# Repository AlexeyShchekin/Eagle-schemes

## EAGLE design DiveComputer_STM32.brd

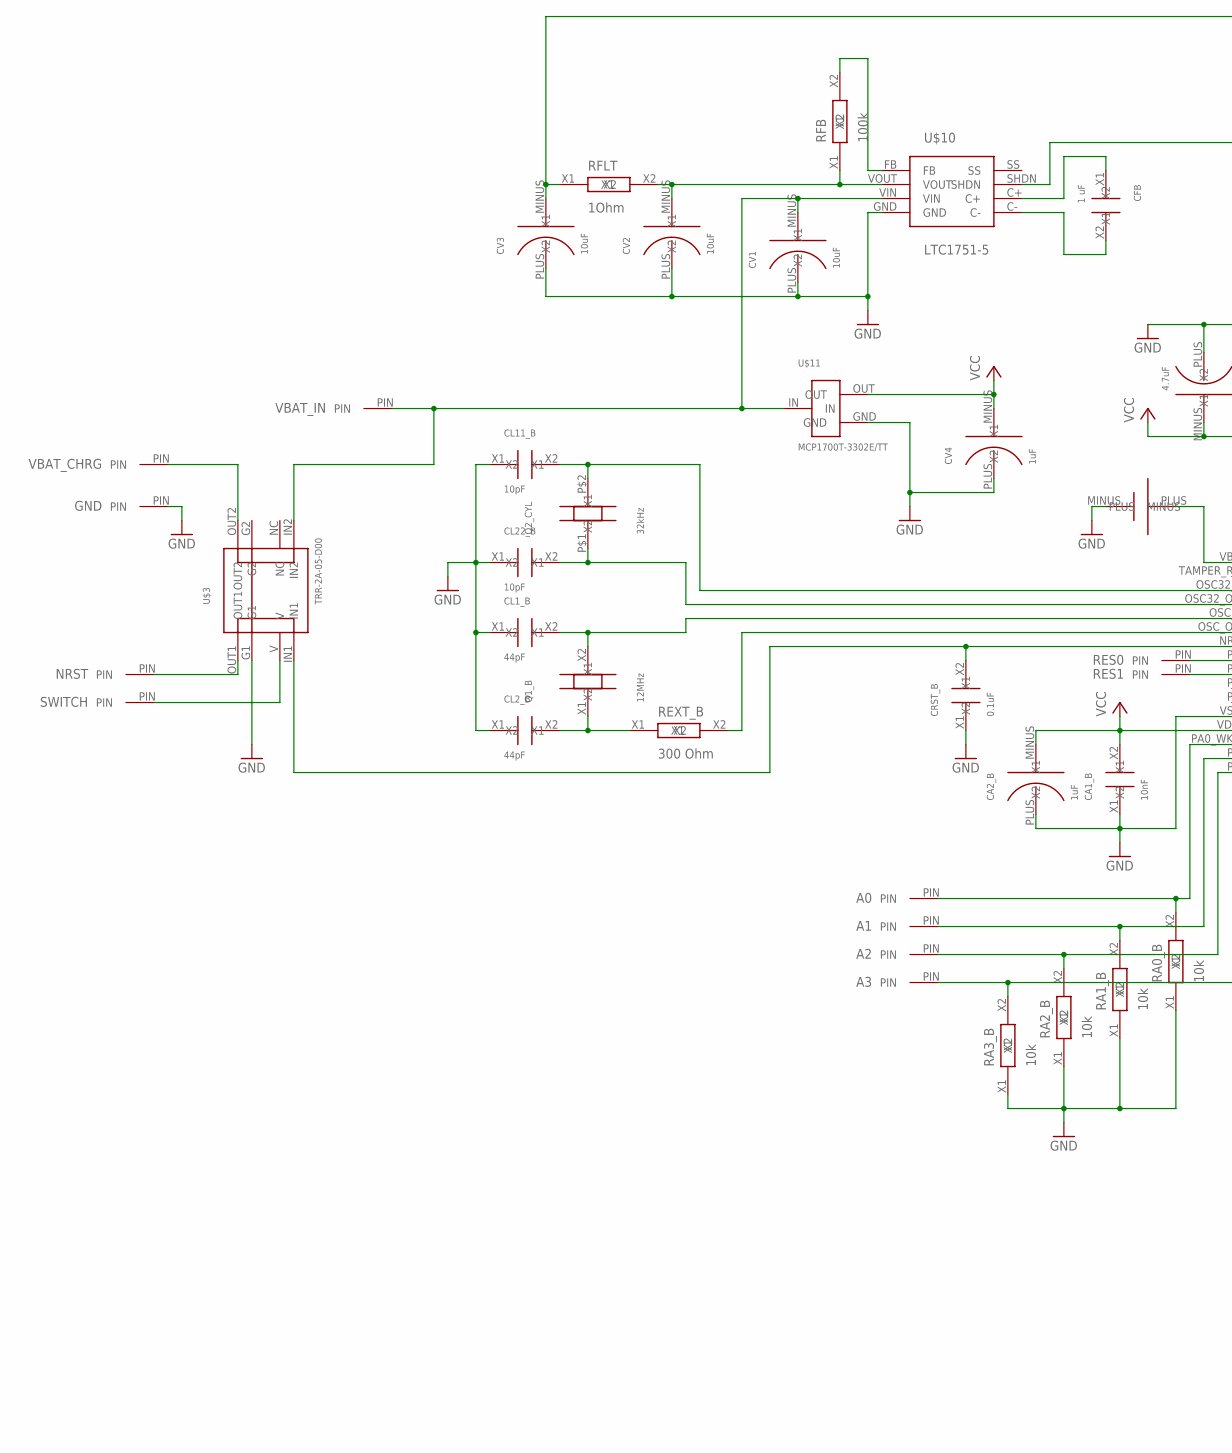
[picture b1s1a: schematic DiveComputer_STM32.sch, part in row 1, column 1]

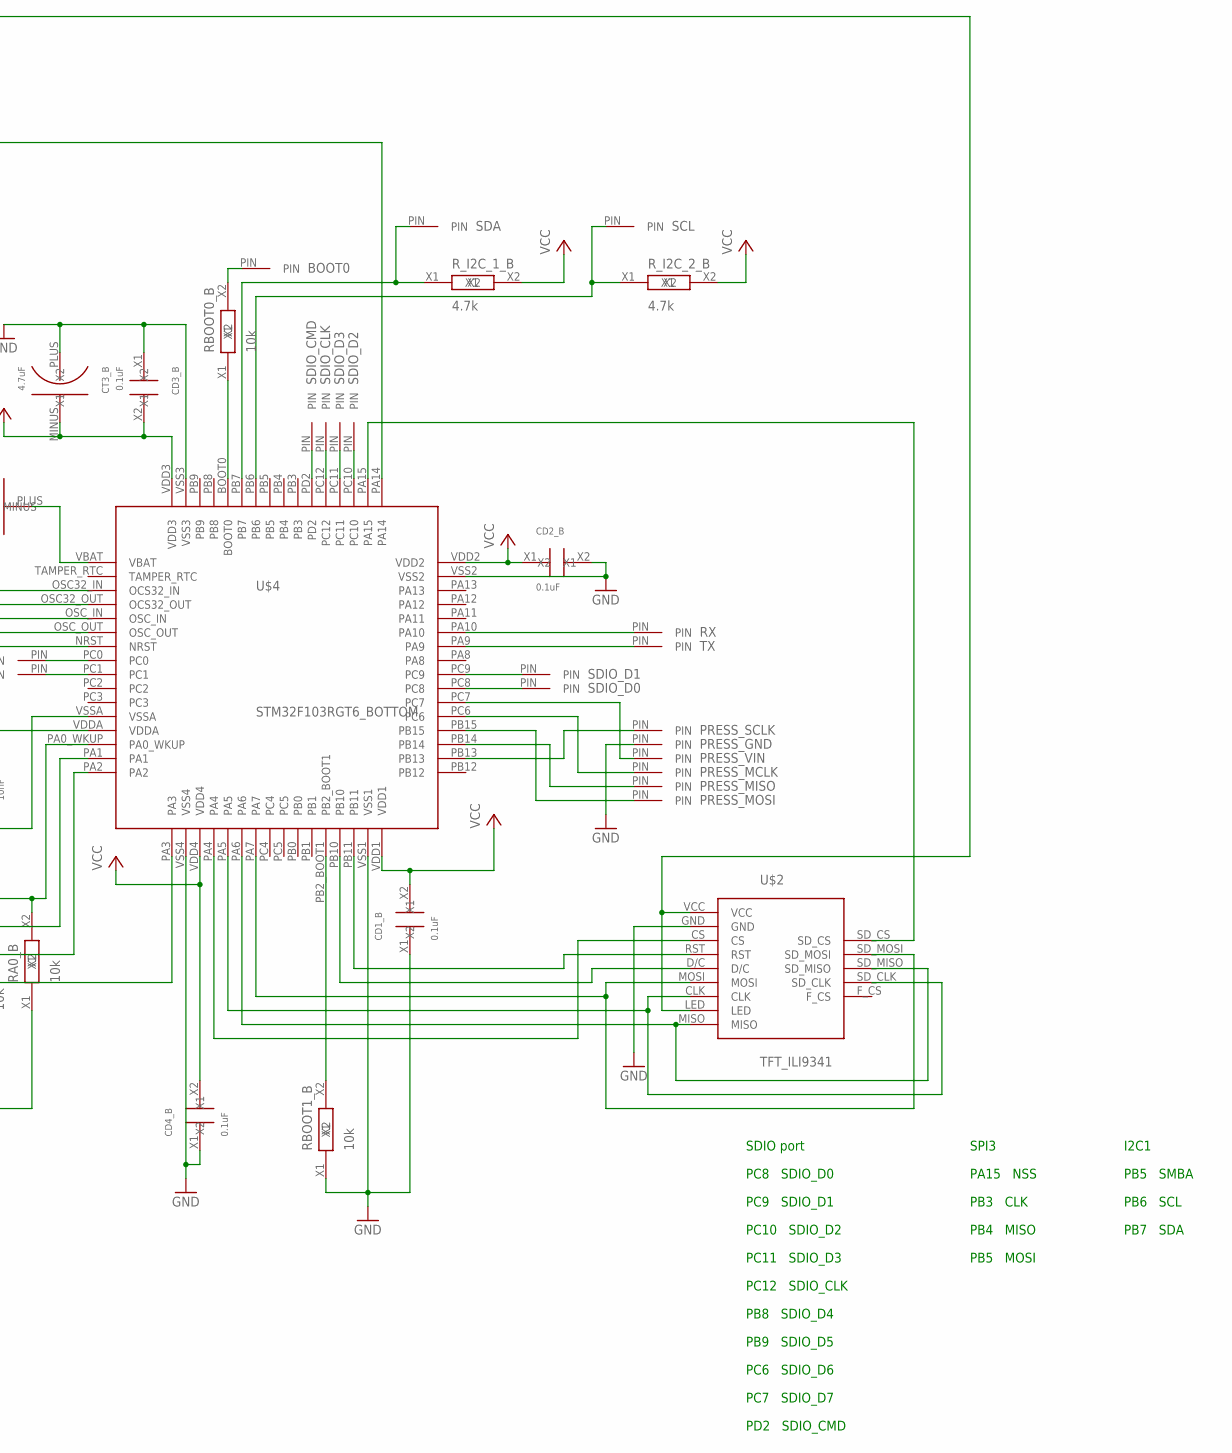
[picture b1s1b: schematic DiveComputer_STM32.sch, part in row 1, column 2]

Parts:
A0, A1, A2, A3: PIN
BOOT0: PIN
CA1_B: 10nF; SMD_2.1X1.25_BOTTOM
CA2_B: 1uF; C_SMD_TA_A_BOTTOM
CD1_B, CD2_B, CD3_B, CD4_B: 0.1uF; SMD_2.1X1.25_BOTTOM
CFB: 1 uF; SMD_2.1X1.25
CL1_B, CL2_B: 44pF; SMD_2.1X1.25_BOTTOM
CL11_B, CL22_B: 10pF; SMD_2.1X1.25_BOTTOM
CRST_B: 0.1uF; SMD_2.1X1.25_BOTTOM
CT3_B: 4.7uF; C_SMD_TA_A_BOTTOM
CV1, CV2, CV3: 10uF; C_SMD_TA_A
CV4: 1uF; C_SMD_TA_A
GND: PIN
NRST: PIN
PRESS_GND: PIN
PRESS_MCLK: PIN
PRESS_MISO: PIN
PRESS_MOSI: PIN
PRESS_SCLK: PIN
PRESS_VIN: PIN
Q1_B: 12MHz; QUARTZ_SMD_BOTTOM
Q2_CYL: 32kHz; QUARTZ_CYL
RA0_B, RA1_B, RA2_B, RA3_B: 10k; SMD_2.1X1.25_BOTTOM
RBOOT0_B, RBOOT1_B: 10k; SMD_2.1X1.25_BOTTOM
RES0, RES1: PIN
REXT_B: 300 Ohm; SMD_2.1X1.25_BOTTOM
RFB: 100k; SMD_2.1X1.25
RFLT: 1Ohm; SMD_2.1X1.25
RX: PIN
R_I2C_1_B, R_I2C_2_B: 4.7k; SMD_2.1X1.25_BOTTOM
SCL: PIN
SDA: PIN
SDIO_CLK: PIN
SDIO_CMD: PIN
SDIO_D0, SDIO_D1, SDIO_D2, SDIO_D3: PIN
SWITCH: PIN
TX: PIN
U$1: VBAT
U$2: TFT_ILI9341
U$3: TRR-2A-05-D00
U$4: STM32F103RGT6_BOTTOM
U$10: LTC1751-5
U$11: MCP1700T-3302E/TT
VBAT_CHRG: PIN
VBAT_IN: PIN

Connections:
GND: CA1_B.X1, CA2_B.PLUS (X1), CD1_B.X1, CD2_B.X2, CD3_B.X1, CD4_B.X1, CL1_B.X1, CL2_B.X1, CL11_B.X1, CL22_B.X1, CRST_B.X1, CT3_B.PLUS (X1), CV1.PLUS (X1), CV2.PLUS (X1), CV3.PLUS (X1), CV4.PLUS (X1), GND.PIN, PRESS_GND.PIN, RA0_B.X1, RA1_B.X1, RA2_B.X1, RA3_B.X1, RBOOT1_B.X1, U$1.MINUS, U$2.GND, U$3.G1, U$4.VSS1, U$4.VSS2, U$4.VSS3, U$4.VSS4, U$4.VSSA, U$10.GND, U$11.GND
unnamed: CL11_B.X2, Q2_CYL.P$2 (X2), U$4.OSC32_IN (OCS32_IN)
unnamed: CL22_B.X2, Q2_CYL.P$1 (X1), U$4.OSC32_OUT (OCS32_OUT)
unnamed: CL2_B.X2, Q1_B.X1, REXT_B.X1
unnamed: CL1_B.X2, Q1_B.X2, U$4.OSC_IN
unnamed: REXT_B.X2, U$4.OSC_OUT
unnamed: CRST_B.X2, U$3.IN1, U$4.NRST
unnamed: U$2.CLK, U$2.SD_CLK, U$4.PA5
unnamed: U$2.MOSI, U$2.SD_MOSI, U$4.PA7
unnamed: U$2.MISO, U$2.SD_MISO, U$4.PA6
unnamed: U$2.CS, U$4.PA4
unnamed: U$2.RST, U$4.PB11
unnamed: U$2.D/C, U$4.PB10
unnamed: A0.PIN, RA0_B.X2, U$4.PA0_WKUP
unnamed: A1.PIN, RA1_B.X2, U$4.PA1
unnamed: A2.PIN, RA2_B.X2, U$4.PA2
unnamed: A3.PIN, RA3_B.X2, U$4.PA3
unnamed: BOOT0.PIN, RBOOT0_B.X2
unnamed: RBOOT1_B.X2, U$4.PB2_BOOT1
unnamed: RBOOT0_B.X1, U$4.BOOT0
unnamed: PRESS_SCLK.PIN, U$4.PB13
unnamed: PRESS_MISO.PIN, U$4.PB14
unnamed: PRESS_MOSI.PIN, U$4.PB15
unnamed: PRESS_MCLK.PIN, U$4.PC6
unnamed: U$2.SD_CS, U$4.PA15
unnamed: U$4.PA14, U$10.SHDN
unnamed: U$3.OUT2, VBAT_CHRG.PIN
unnamed: NRST.PIN, U$3.OUT1
unnamed: CV2.MINUS (X2), RFB.X1, RFLT.X2, U$10.VOUT
unnamed: RFB.X2, U$10.FB
unnamed: CFB.X1, U$10.C+
unnamed: CFB.X2, U$10.C-
unnamed: CV3.MINUS (X2), RFLT.X1, U$2.LED, U$2.VCC
unnamed: CV1.MINUS (X2), U$3.IN2, U$10.VIN, U$11.IN, VBAT_IN.PIN
unnamed: SWITCH.PIN, U$3.V
unnamed: TX.PIN, U$4.PA9
unnamed: RX.PIN, U$4.PA10
unnamed: PRESS_VIN.PIN, U$4.PC7
unnamed: R_I2C_1_B.X1, SDA.PIN, U$4.PB7
unnamed: R_I2C_2_B.X1, SCL.PIN, U$4.PB6
unnamed: U$1.PLUS, U$4.VBAT
unnamed: RES0.PIN, U$4.PC0
unnamed: RES1.PIN, U$4.PC1
unnamed: SDIO_D0.PIN, U$4.PC8
unnamed: SDIO_D1.PIN, U$4.PC9
unnamed: SDIO_CMD.PIN, U$4.PD2
unnamed: SDIO_CLK.PIN, U$4.PC12
unnamed: SDIO_D3.PIN, U$4.PC11
unnamed: SDIO_D2.PIN, U$4.PC10
VCC: CA1_B.X2, CA2_B.MINUS (X2), CD1_B.X2, CD2_B.X1, CD3_B.X2, CD4_B.X2, CT3_B.MINUS (X2), CV4.MINUS (X2), R_I2C_1_B.X2, R_I2C_2_B.X2, U$4.VDD1, U$4.VDD2, U$4.VDD3, U$4.VDD4, U$4.VDDA, U$11.OUT

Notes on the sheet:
SDIO port
PC8 SDIO_D0
PC9 SDIO_D1
PC10 SDIO_D2
PC11 SDIO_D3
PC12 SDIO_CLK
PB8 SDIO_D4
PB9 SDIO_D5
PC6 SDIO_D6
PC7 SDIO_D7
SPI3
PA15 NSS
PB3 CLK
PB4 MISO
PB5 MOSI
I2C1
PB5 SMBA
PB6 SCL
PB7 SDA
PD2 SDIO_CMD

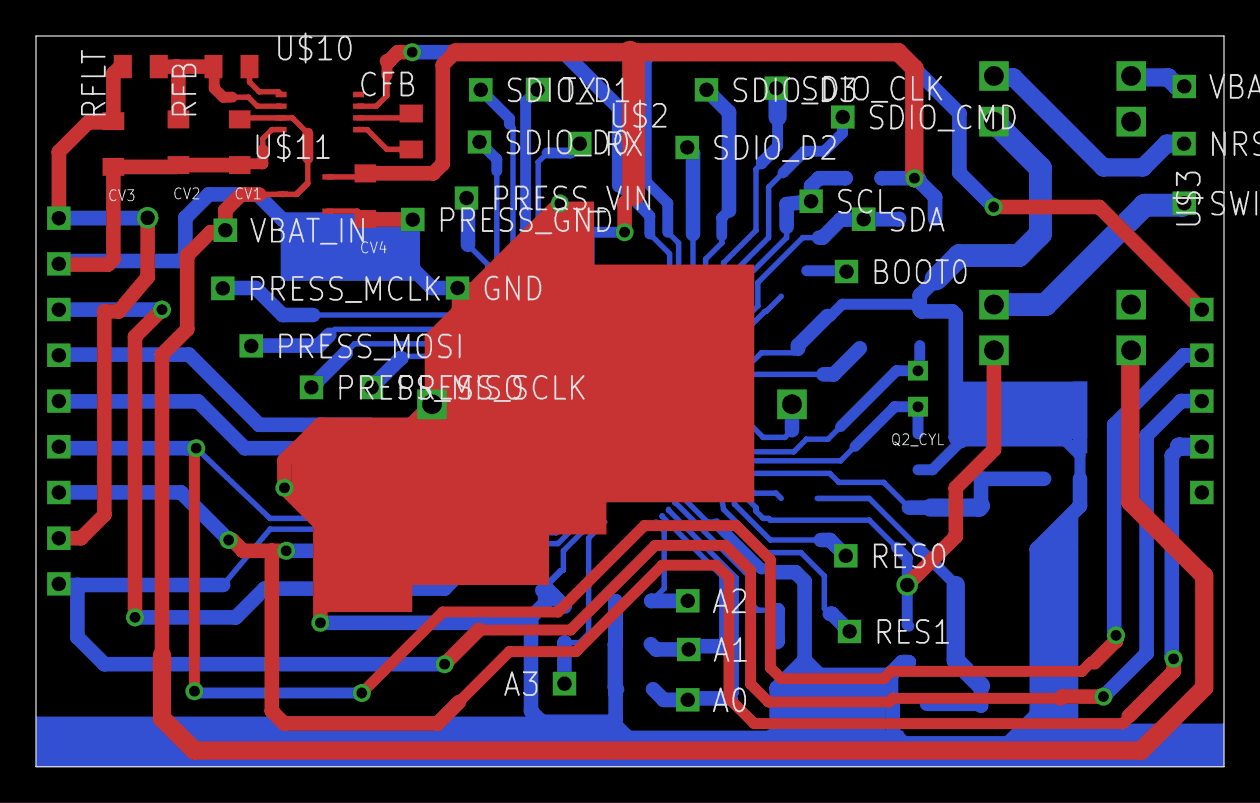
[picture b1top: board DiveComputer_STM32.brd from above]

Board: 2 copper layers, 66.0 x 40.6 mm, 64 parts (0 on the bottom side), 50 nets.

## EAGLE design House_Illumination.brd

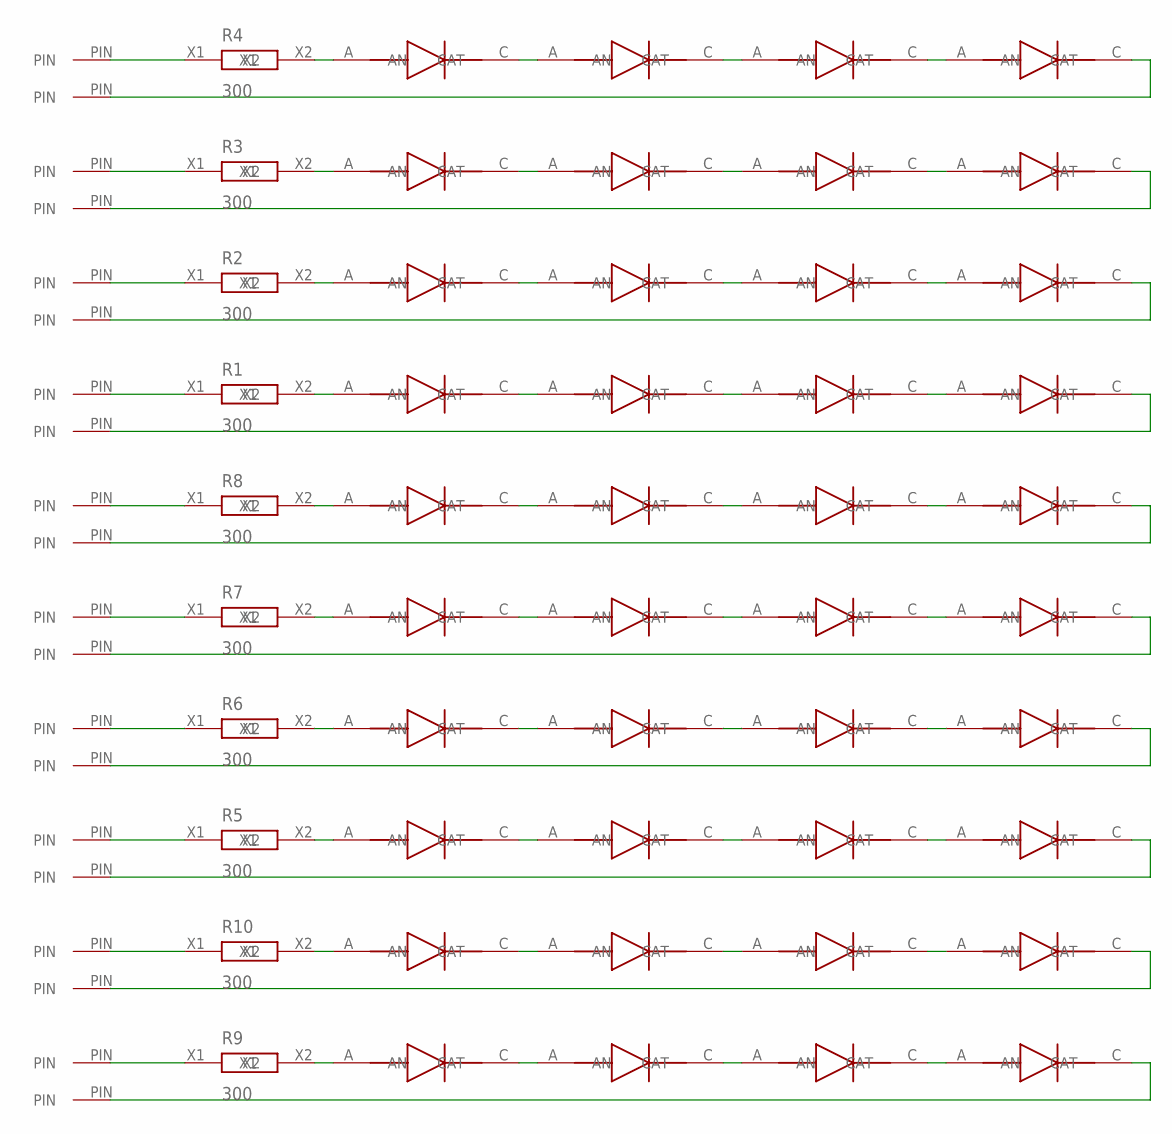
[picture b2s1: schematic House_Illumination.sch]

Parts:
R1, R2, R3, R4, R5, R6, R7, R8, R9, R10: 300; SMD_2.1X1.25
U$1, U$2, U$7, U$8, U$13, U$14, U$19, U$20, U$25, U$26, U$31, U$32, U$37, U$38, U$43, U$44, U$49, U$50, U$55, U$56: PIN_1
U$3, U$4, U$5, U$6, U$9, U$10, U$11, U$12, U$15, U$16, U$17, U$18, U$21, U$22, U$23, U$24, U$27, U$28, U$29, U$30, U$33, U$34, U$35, U$36, U$39, U$40, U$41, U$42, U$45, U$46, U$47, U$48, U$51, U$52, U$53, U$54, U$57, U$58, U$59, U$60: LED0805

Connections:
unnamed: R1.X1, U$1.PIN
unnamed: R1.X2, U$3.A (AN)
unnamed: U$3.C (CAT), U$4.A (AN)
unnamed: U$4.C (CAT), U$5.A (AN)
unnamed: U$5.C (CAT), U$6.A (AN)
unnamed: U$2.PIN, U$6.C (CAT)
unnamed: R2.X1, U$7.PIN
unnamed: R2.X2, U$9.A (AN)
unnamed: U$9.C (CAT), U$10.A (AN)
unnamed: U$10.C (CAT), U$11.A (AN)
unnamed: U$11.C (CAT), U$12.A (AN)
unnamed: U$8.PIN, U$12.C (CAT)
unnamed: R3.X1, U$13.PIN
unnamed: R3.X2, U$15.A (AN)
unnamed: U$15.C (CAT), U$16.A (AN)
unnamed: U$16.C (CAT), U$17.A (AN)
unnamed: U$17.C (CAT), U$18.A (AN)
unnamed: U$14.PIN, U$18.C (CAT)
unnamed: R4.X1, U$19.PIN
unnamed: R4.X2, U$21.A (AN)
unnamed: U$21.C (CAT), U$22.A (AN)
unnamed: U$22.C (CAT), U$23.A (AN)
unnamed: U$23.C (CAT), U$24.A (AN)
unnamed: U$20.PIN, U$24.C (CAT)
unnamed: R5.X1, U$25.PIN
unnamed: R5.X2, U$27.A (AN)
unnamed: U$27.C (CAT), U$28.A (AN)
unnamed: U$28.C (CAT), U$29.A (AN)
unnamed: U$29.C (CAT), U$30.A (AN)
unnamed: U$26.PIN, U$30.C (CAT)
unnamed: R6.X1, U$31.PIN
unnamed: R6.X2, U$33.A (AN)
unnamed: U$33.C (CAT), U$34.A (AN)
unnamed: U$34.C (CAT), U$35.A (AN)
unnamed: U$35.C (CAT), U$36.A (AN)
unnamed: U$32.PIN, U$36.C (CAT)
unnamed: R7.X1, U$37.PIN
unnamed: R7.X2, U$39.A (AN)
unnamed: U$39.C (CAT), U$40.A (AN)
unnamed: U$40.C (CAT), U$41.A (AN)
unnamed: U$41.C (CAT), U$42.A (AN)
unnamed: U$38.PIN, U$42.C (CAT)
unnamed: R8.X1, U$43.PIN
unnamed: R8.X2, U$45.A (AN)
unnamed: U$45.C (CAT), U$46.A (AN)
unnamed: U$46.C (CAT), U$47.A (AN)
unnamed: U$47.C (CAT), U$48.A (AN)
unnamed: U$44.PIN, U$48.C (CAT)
unnamed: R9.X1, U$49.PIN
unnamed: R9.X2, U$51.A (AN)
unnamed: U$51.C (CAT), U$52.A (AN)
unnamed: U$52.C (CAT), U$53.A (AN)
unnamed: U$53.C (CAT), U$54.A (AN)
unnamed: U$50.PIN, U$54.C (CAT)
unnamed: R10.X1, U$55.PIN
unnamed: R10.X2, U$57.A (AN)
unnamed: U$57.C (CAT), U$58.A (AN)
unnamed: U$58.C (CAT), U$59.A (AN)
unnamed: U$59.C (CAT), U$60.A (AN)
unnamed: U$56.PIN, U$60.C (CAT)

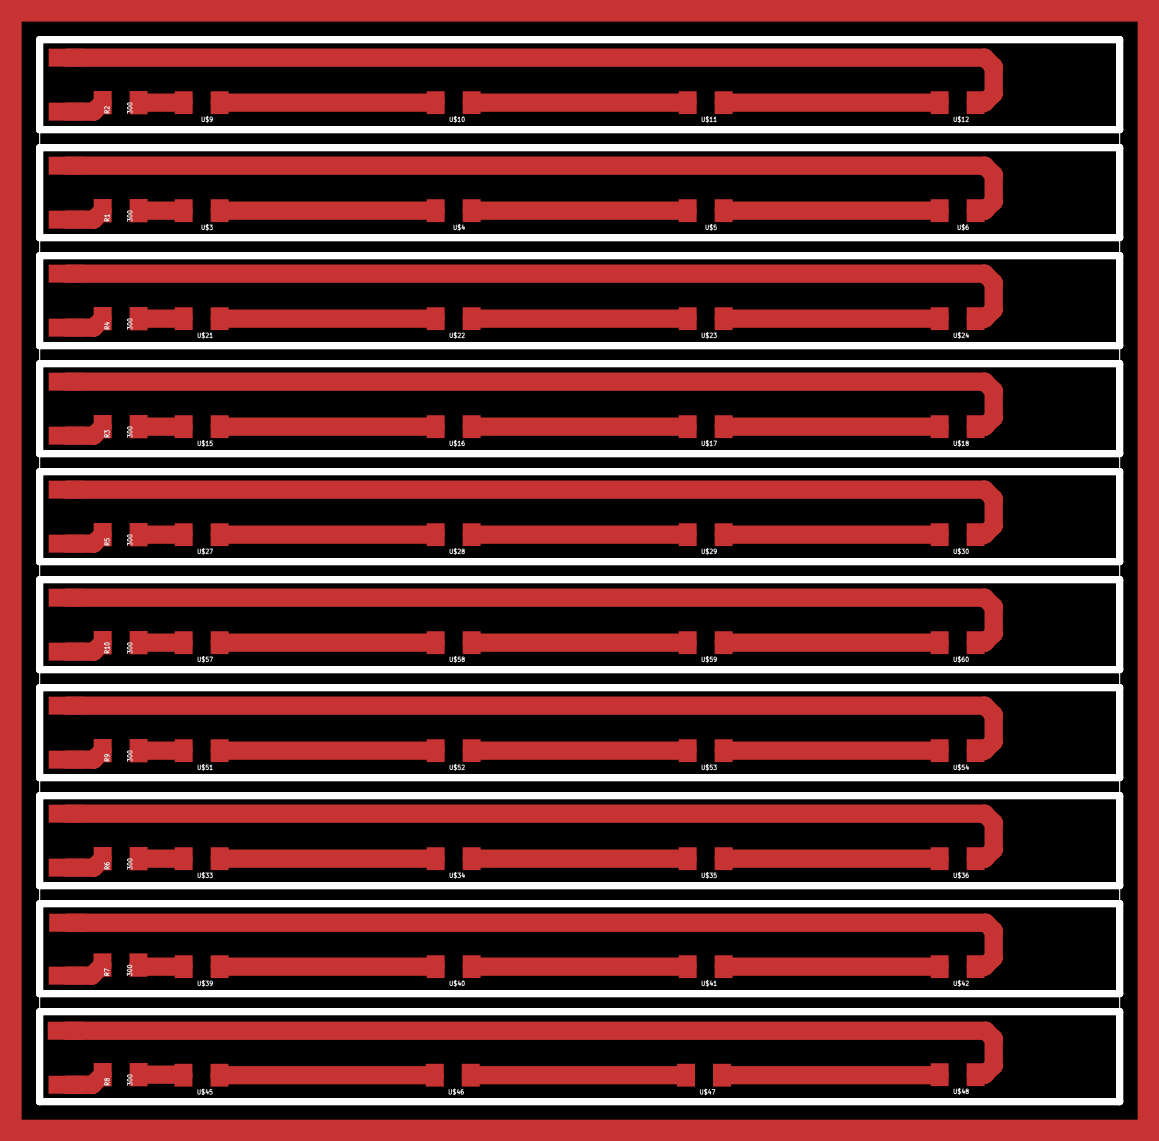
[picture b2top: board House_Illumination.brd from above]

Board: 2 copper layers, 60.0 x 59.0 mm, 70 parts (0 on the bottom side), 60 nets.

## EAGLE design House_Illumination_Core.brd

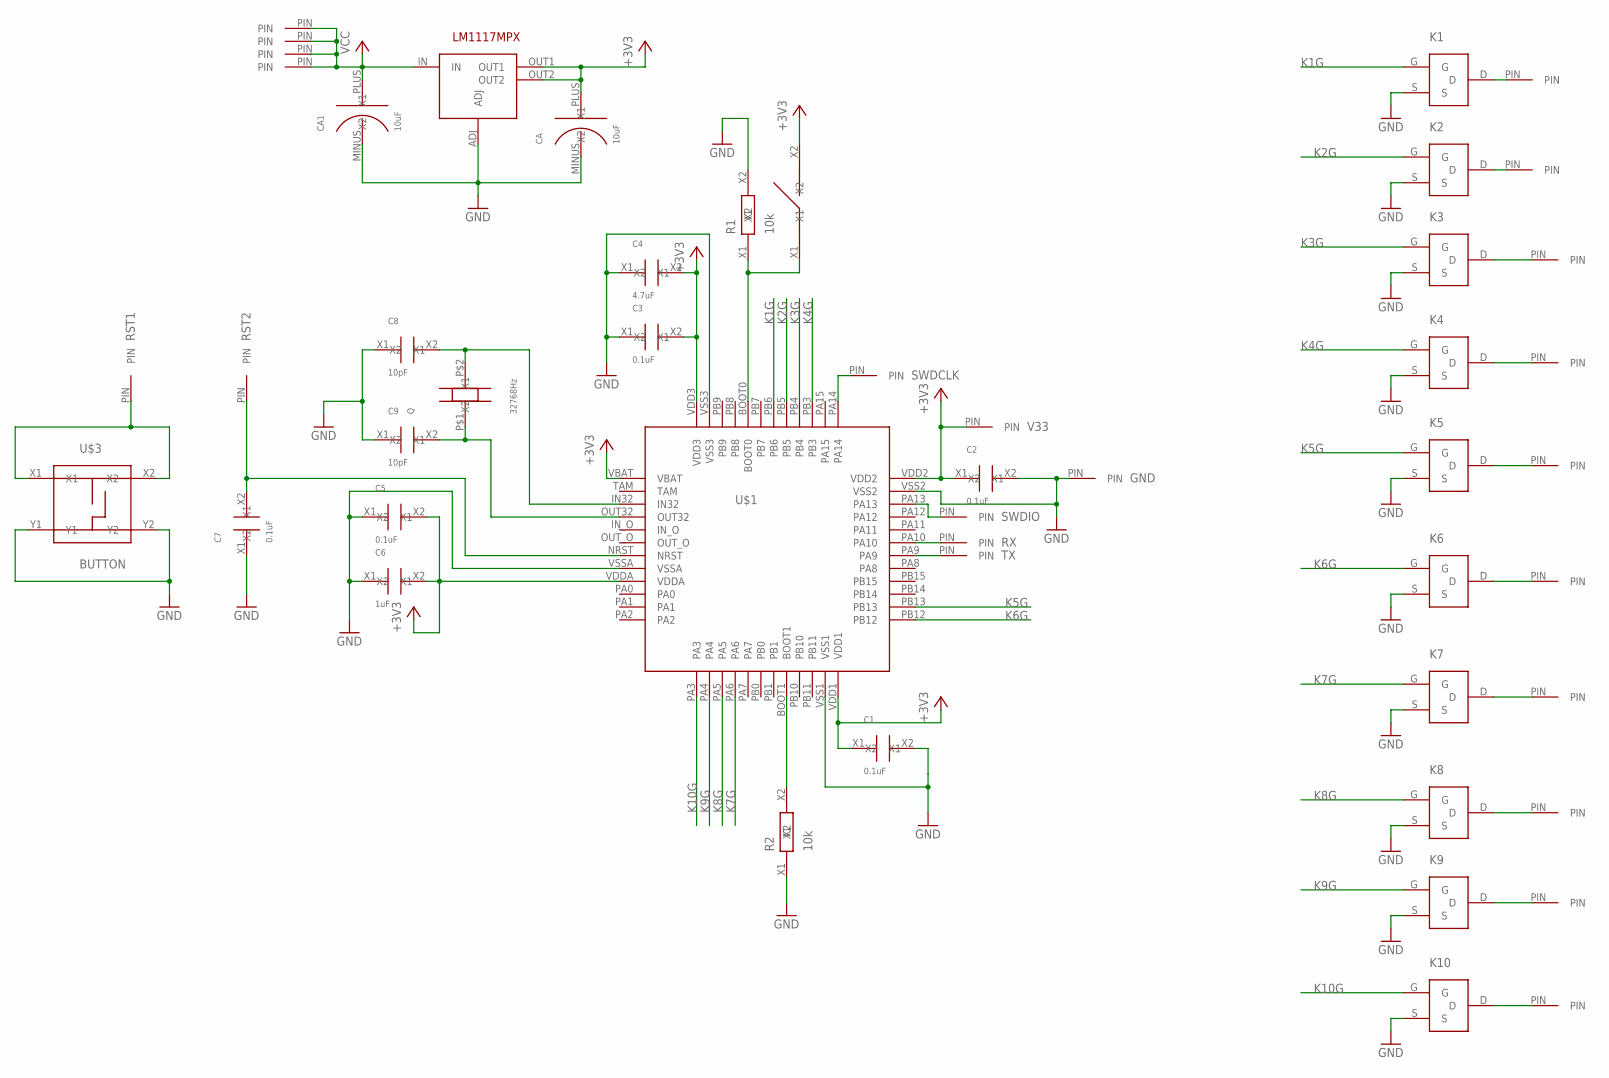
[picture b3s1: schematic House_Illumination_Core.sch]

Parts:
C1, C2, C3, C5, C7: 0.1uF; SMD_2.1X1.25
C4: 4.7uF; SMD_2.1X1.25
C6: 1uF; SMD_2.1X1.25
C8, C9: 10pF; SMD_2.1X1.25
CA, CA1: 10uF; C_SMD_TA_A
GND: PIN
K1, K2, K3, K4, K5, K6, K7, K8, K9, K10: IRFML8244TRPBF
LED1, LED2, LED3, LED4, LED5, LED6, LED7, LED8, LED9, LED10: PIN_1
Q: 32768Hz; QUARTZ_CYL
R1, R2: 10k; SMD_2.1X1.25
RST1, RST2: PIN
RX: PIN
SWDCLK: PIN
SWDIO: PIN
TX: PIN
U$1: STM32F103CBT6
U$2: DIP_1
U$3: BUTTON
U$13: LM1117MPX-ADJ
V33: PIN
VCCPIN, VCCPIN1, VCCPIN2, VCCPIN3: PIN_1

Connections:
+3V3: C1.X1, C2.X1, C3.X2, C4.X2, C5.X2, C6.X2, CA.PLUS (X2), U$1.VBAT, U$1.VDD1, U$1.VDD2, U$1.VDD3, U$1.VDDA, U$2.X2, U$13.OUT1, U$13.OUT2, V33.PIN
GND: C1.X2, C2.X2, C3.X1, C4.X1, C5.X1, C6.X1, C7.X1, C8.X1, C9.X1, CA.MINUS (X1), CA1.MINUS (X1), GND.PIN, K1.S, K2.S, K3.S, K4.S, K5.S, K6.S, K7.S, K8.S, K9.S, K10.S, R1.X2, R2.X1, U$1.VSS1, U$1.VSS2, U$1.VSS3, U$1.VSSA, U$3.Y1, U$3.Y2, U$13.ADJ
K1G: K1.G, U$1.PB6
K2G: K2.G, U$1.PB5
K3G: K3.G, U$1.PB4
K4G: K4.G, U$1.PB3
K5G: K5.G, U$1.PB13
K6G: K6.G, U$1.PB12
K7G: K7.G, U$1.PA6
K8G: K8.G, U$1.PA5
K9G: K9.G, U$1.PA4
K10G: K10.G, U$1.PA3
unnamed: R2.X2, U$1.BOOT1
unnamed: C9.X2, Q.P$1 (X1), U$1.OUT32
unnamed: C8.X2, Q.P$2 (X2), U$1.IN32
unnamed: SWDCLK.PIN, U$1.PA14
unnamed: C7.X2, RST2.PIN, U$1.NRST
unnamed: R1.X1, U$1.BOOT0, U$2.X1
unnamed: K7.D, LED7.PIN
unnamed: SWDIO.PIN, U$1.PA13
unnamed: RX.PIN, U$1.PA10
unnamed: TX.PIN, U$1.PA9
unnamed: RST1.PIN, U$3.X1, U$3.X2
unnamed: K1.D, LED1.PIN
unnamed: K3.D, LED3.PIN
unnamed: K4.D, LED4.PIN
unnamed: K5.D, LED5.PIN
unnamed: K6.D, LED6.PIN
unnamed: K10.D, LED10.PIN
unnamed: K9.D, LED9.PIN
unnamed: K8.D, LED8.PIN
unnamed: K2.D, LED2.PIN
VCC: CA1.PLUS (X2), U$13.IN, VCCPIN.PIN, VCCPIN1.PIN, VCCPIN2.PIN, VCCPIN3.PIN

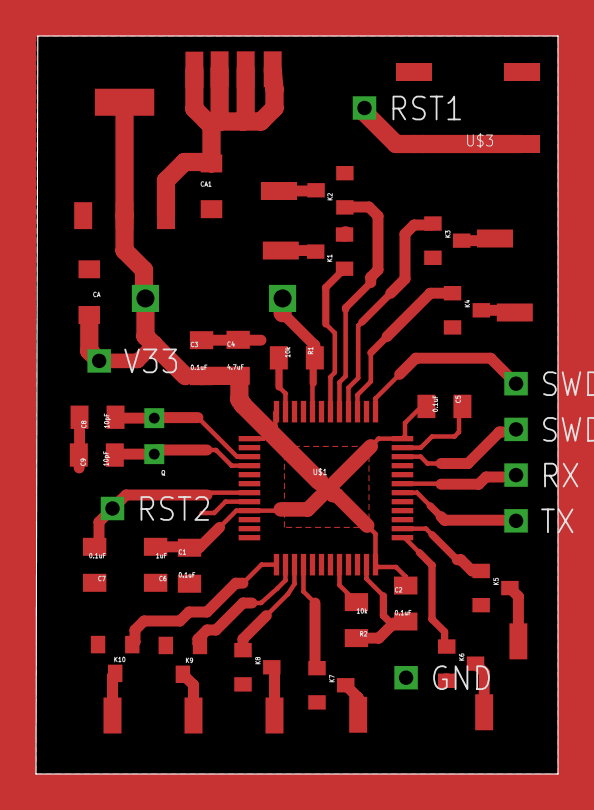
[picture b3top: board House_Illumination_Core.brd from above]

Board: 2 copper layers, 29.0 x 41.0 mm, 50 parts (0 on the bottom side), 33 nets.

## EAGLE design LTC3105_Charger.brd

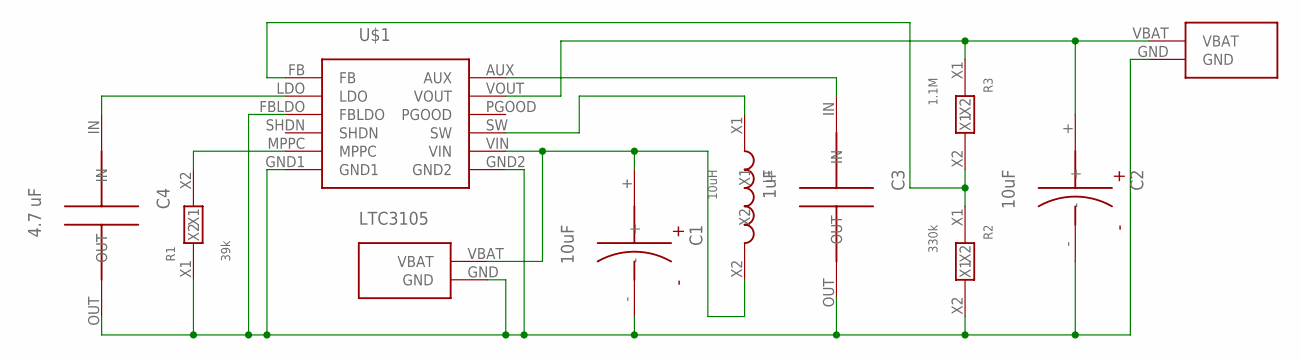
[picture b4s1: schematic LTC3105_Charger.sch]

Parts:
C1, C2: 10uF; C_ELT_2MM
C3: 1uF; C_CER_5MM
C4: 4.7 uF; C_CER_5MM
L1: 10uH; L_10X3
R1: 39k; R_6X2
R2: 330k; R_6X2
R3: 1.1M; R_6X2
U$1: LTC3105
U$10, U$11: BAT_PLUG

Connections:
unnamed: C1.-, C2.-, C3.OUT, C4.OUT, R1.X1, R2.X2, U$1.FBLDO, U$1.GND1, U$1.GND2, U$10.GND, U$11.GND
unnamed: C4.IN, U$1.LDO
unnamed: R1.X2, U$1.MPPC
unnamed: C3.IN, U$1.AUX
unnamed: L1.X1, U$1.SW
unnamed: R2.X1, R3.X2, U$1.FB
unnamed: C2.+, R3.X1, U$1.VOUT, U$11.VBAT
unnamed: C1.+, L1.X2, U$1.VIN, U$10.VBAT

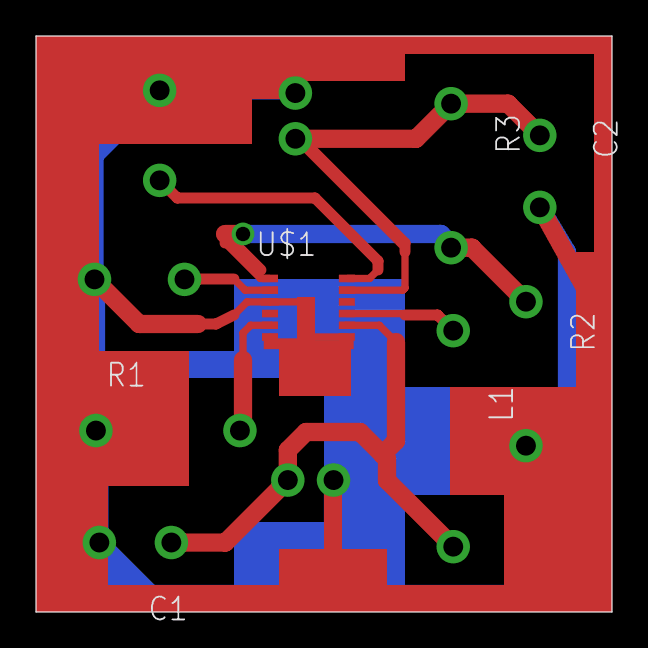
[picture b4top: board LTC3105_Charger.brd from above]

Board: 2 copper layers, 32.0 x 32.0 mm, 11 parts (0 on the bottom side), 8 nets.

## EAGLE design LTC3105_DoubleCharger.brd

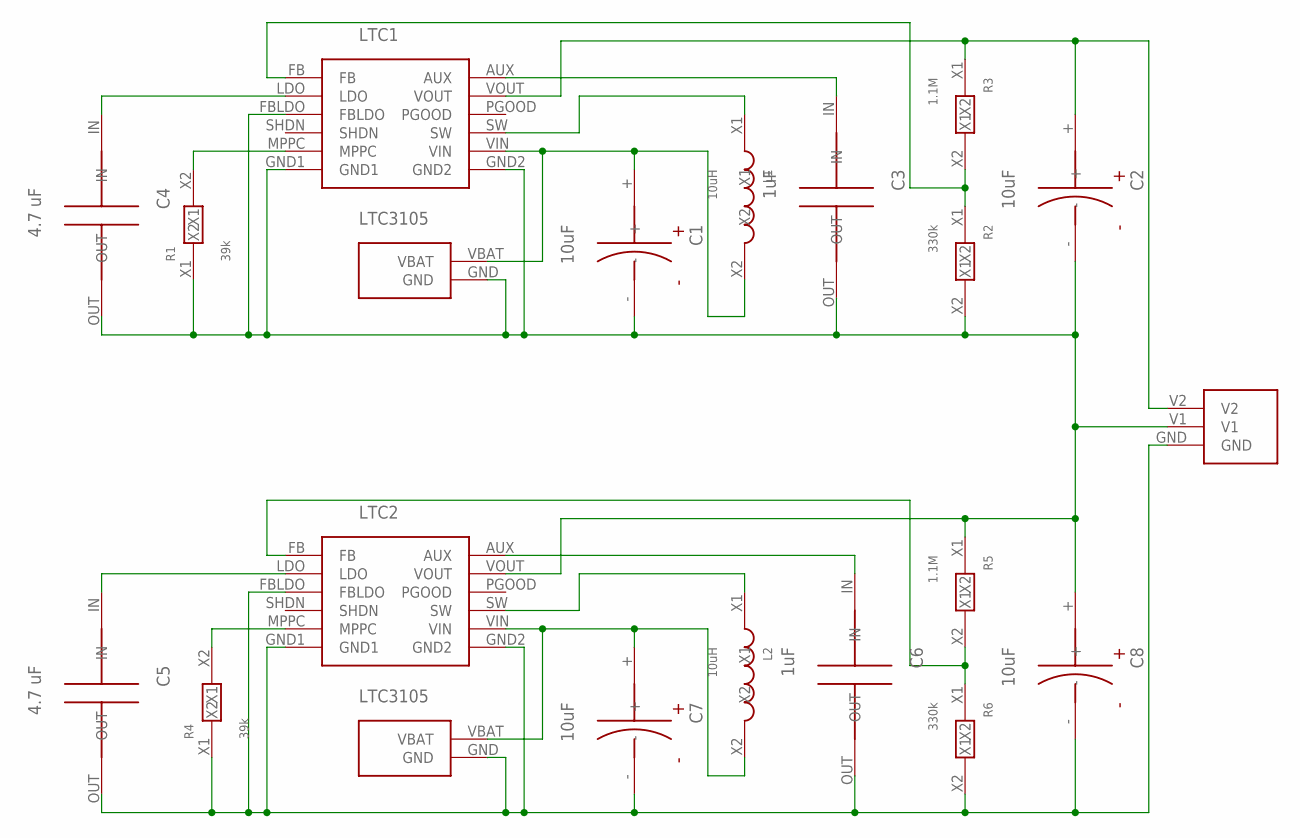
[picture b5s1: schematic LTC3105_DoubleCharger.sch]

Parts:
C1, C2, C7, C8: 10uF; C_ELT_2MM
C3, C6: 1uF; C_CER_5MM
C4, C5: 4.7 uF; C_CER_5MM
L1, L2: 10uH; L_10X3
LTC1, LTC2: LTC3105
R1, R4: 39k; R_6X2
R2, R6: 330k; R_6X2
R3, R5: 1.1M; R_6X2
U$1: BAT3_PLUG
U$3, U$10: BAT_PLUG

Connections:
LTC1: LTC1.FB, R2.X1, R3.X2
unnamed: LTC1.MPPC, R1.X2
unnamed: C4.IN, LTC1.LDO
unnamed: C3.IN, LTC1.AUX
unnamed: L1.X1, LTC1.SW
unnamed: LTC2.MPPC, R4.X2
unnamed: C2.+, LTC1.VOUT, R3.X1, U$1.V2
unnamed: C5.IN, LTC2.LDO
unnamed: C5.OUT, C6.OUT, C7.-, C8.-, LTC2.FBLDO, LTC2.GND1, LTC2.GND2, R4.X1, R6.X2, U$1.GND, U$3.GND
unnamed: C1.+, L1.X2, LTC1.VIN, U$10.VBAT
unnamed: C7.+, L2.X2, LTC2.VIN, U$3.VBAT
unnamed: L2.X1, LTC2.SW
unnamed: C6.IN, LTC2.AUX
unnamed: C1.-, C2.-, C3.OUT, C4.OUT, C8.+, LTC1.FBLDO, LTC1.GND1, LTC1.GND2, LTC2.VOUT, R1.X1, R2.X2, R5.X1, U$1.V1, U$10.GND
unnamed: LTC2.FB, R5.X2, R6.X1

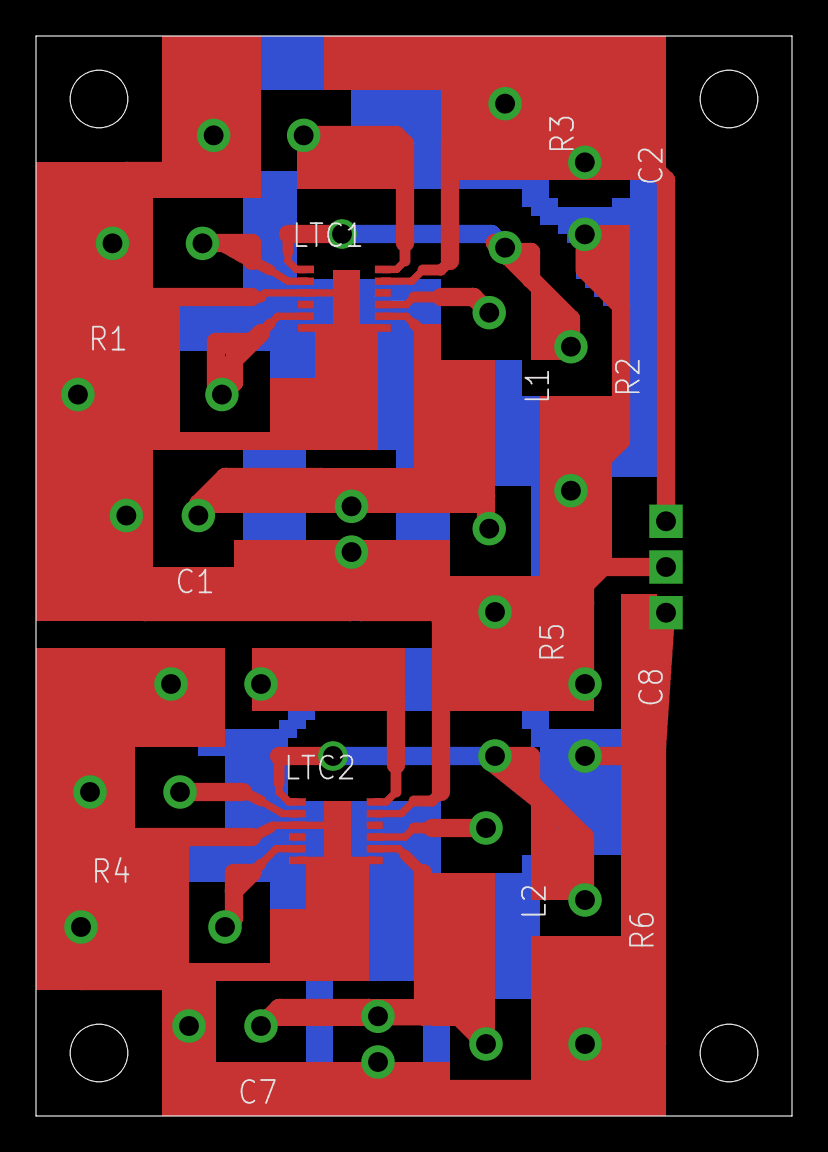
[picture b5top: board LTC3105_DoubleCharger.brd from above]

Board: 2 copper layers, 42.0 x 60.0 mm, 21 parts (0 on the bottom side), 15 nets.

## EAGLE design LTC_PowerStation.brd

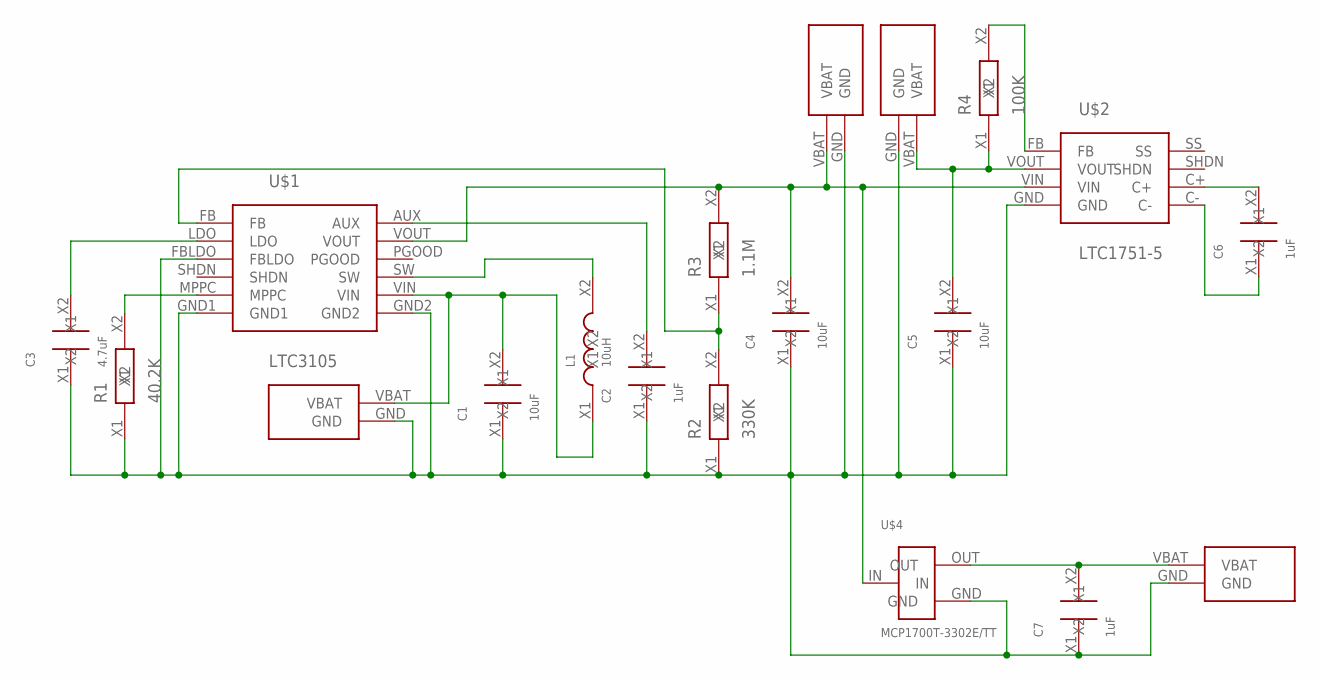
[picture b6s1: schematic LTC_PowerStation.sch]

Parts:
C1, C4, C5: 10uF; SMD_2.1X1.25
C2, C6, C7: 1uF; SMD_2.1X1.25
C3: 4.7uF; SMD_2.1X1.25
L1: 10uH; SMD_2.1X1.25
R1: 40.2K; SMD_2.1X1.25
R2: 330K; SMD_2.1X1.25
R3: 1.1M; SMD_2.1X1.25
R4: 100K; SMD_2.1X1.25
U$1: LTC3105
U$2: LTC1751-5
U$3, U$5, U$10, U$11: BAT_PLUG
U$4: MCP1700T-3302E/TT

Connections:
unnamed: C1.X1, C2.X1, C3.X1, C4.X1, C5.X1, C7.X1, R1.X1, R2.X1, U$1.FBLDO, U$1.GND1, U$1.GND2, U$2.GND, U$3.GND, U$4.GND, U$5.GND, U$10.GND, U$11.GND
unnamed: C3.X2, U$1.LDO
unnamed: R1.X2, U$1.MPPC
unnamed: C2.X2, U$1.AUX
unnamed: L1.X2, U$1.SW
unnamed: R2.X2, R3.X1, U$1.FB
unnamed: C4.X2, R3.X2, U$1.VOUT, U$2.VIN, U$4.IN, U$11.VBAT
unnamed: C5.X2, R4.X1, U$2.VOUT, U$3.VBAT
unnamed: C1.X2, L1.X1, U$1.VIN, U$10.VBAT
unnamed: R4.X2, U$2.FB
unnamed: C6.X2, U$2.C+
unnamed: C6.X1, U$2.C-
unnamed: C7.X2, U$4.OUT, U$5.VBAT

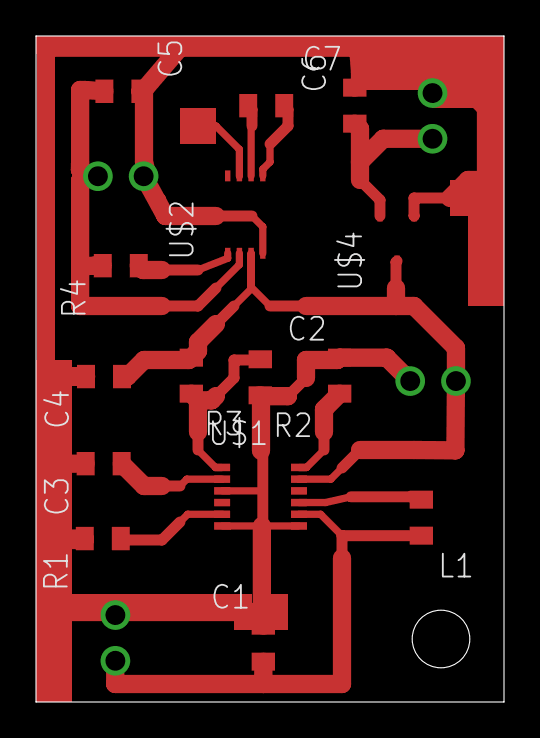
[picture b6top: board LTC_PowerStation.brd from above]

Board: 2 copper layers, 26.0 x 37.0 mm, 19 parts (0 on the bottom side), 13 nets.

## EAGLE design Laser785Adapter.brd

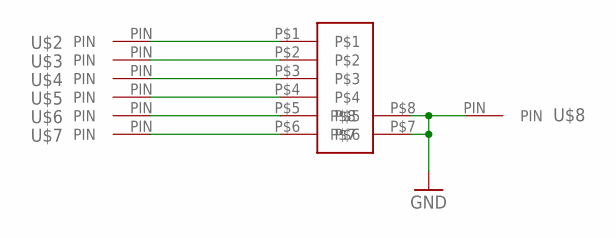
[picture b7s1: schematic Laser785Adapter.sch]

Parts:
U$1: MOLEX_5023860670
U$2, U$3, U$4, U$5, U$6, U$7, U$8: PIN

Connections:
GND: U$1.P$7, U$1.P$8, U$8.PIN
unnamed: U$1.P$1, U$2.PIN
unnamed: U$1.P$2, U$3.PIN
unnamed: U$1.P$3, U$4.PIN
unnamed: U$1.P$4, U$5.PIN
unnamed: U$1.P$5, U$6.PIN
unnamed: U$1.P$6, U$7.PIN

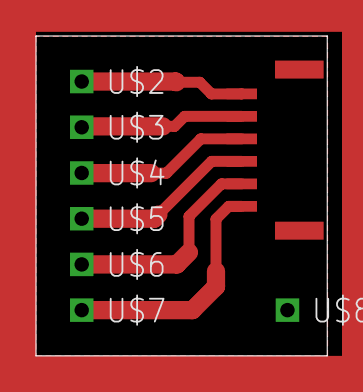
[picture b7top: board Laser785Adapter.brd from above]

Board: 2 copper layers, 16.2 x 17.8 mm, 8 parts (0 on the bottom side), 7 nets.
